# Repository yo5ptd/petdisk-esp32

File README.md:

# petdisk-esp32
CBM PETDISK based on Esp32 and MicroSD

## Introduction
My fourth PCB design, first (mostly) SMD one to test how ordering assembled PCB from JLCPCB works. Motivation for this was that it's a bit of a pain to order @bitfixer 's Petdisk Max V2 Esp32 from the US, and I've found no alternatives in the EU. 

## Hardware documentation

As per bitfixer's Petdisk V2 Max https://github.com/bitfixer/petdisk-max . Ports as per https://github.com/svenpetersen1965/PET-IEEE-488-Extension .

I've only changed the SD slot to Hanbo Electric TS-013 as this was available at JLCPCB.

### Schematic and PCB layout

[Schematic](CBM-Petdisk-Schematic.pdf)

[PCB Layout](CBM-Petdisk-Board.pdf)

[Front](petdisk%20esp32.jpg)

[Back](petdisk%20esp32-back.jpg)

## Panelization and odering from JLCPCB

Panelized with Kikit addon with hand-breakable "mousebytes", it still fits the 100x100 mm JLCPCB limit (Kikit.json settings included, details in https://github.com/yaqwsx/KiKit). 

The idea is to order the placement for the cheap SMD components, and only solder 3 electrolytic capacitors, the ESP32 module and a "805 Strip Connector 3.96mm Pitch 12 Pin" connector from Aliexpress. Cost per board from JLPCB thus is around 3.3$ when ordered in batches of 5 (10 boards in total, coupons used, shipping and taxes included) With connector, capacitors, esp32 should not get over 8.5$ per board, but probably more as I don't plan to order 10 of these.

You need the:
[Gerbers](gerbers.2xpetdisk-esp32.zip)

[BOM](BOM_JLCSMT.xlsx)

[CPL](JLCSMT_CPL.xlsx)

Disregards the duplicate message, also allow auto placement alignment.

## Programming

note that the programming port pinout is different from the original.

First board was fully assembled and tested on 29.07.2025. Note that I managed to get it working with the original Petdisk max v2.1 firmware with a 32GB card. 512mb, 1gb and 128gb cards were not recognized.

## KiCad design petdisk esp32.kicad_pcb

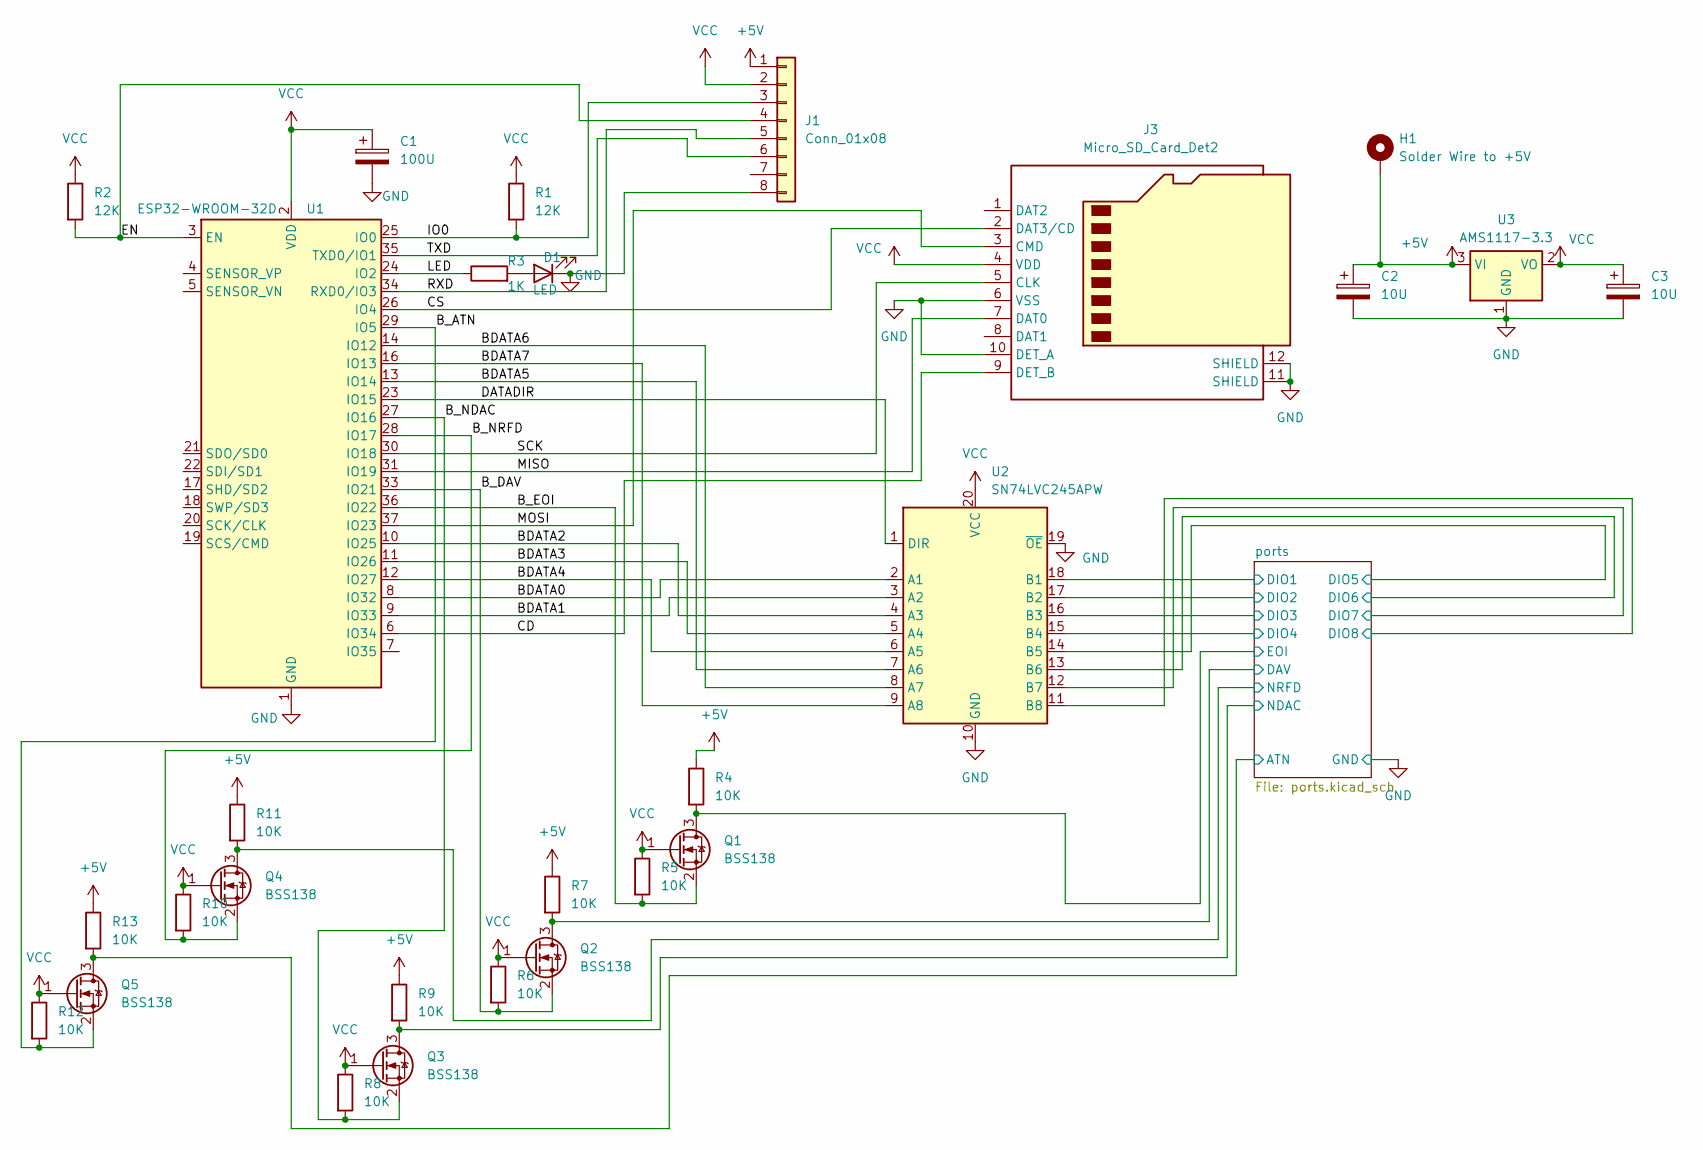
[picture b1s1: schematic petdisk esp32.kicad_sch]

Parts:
C1: 100U; CP_Radial_D5.0mm_P2.50mm
C2, C3: 10U; CP_Radial_D5.0mm_P2.50mm
D1: LED; LED_0603_1608Metric
H1: Solder Wire to +5V; SolderWire-0.1sqmm_1x01_D0.4mm_OD1mm
J1: Conn_01x08; PinHeader_1x08_P2.54mm_Vertical
J3: Micro_SD_Card_Det2; TF-SMD_TF-013
Q1, Q2, Q3, Q4, Q5: BSS138; SOT-23
R1, R2: 12K; R_0805_2012Metric
R3: 1K; R_0805_2012Metric
R4, R5, R6, R7, R8, R9, R10, R11, R12, R13: 10K; R_0805_2012Metric
U1: ESP32-WROOM-32D
U2: SN74LVC245APW; TSSOP-20_4.4x6.5mm_P0.65mm
U3: AMS1117-3.3; SOT-223-3_TabPin2

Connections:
+5V: C2.1, H1.1, J1.1, R4.1, R7.1, R9.1, R11.1, R13.1, U3.3 (VI)
/BDATA0: U1.8 (IO32), U2.2 (A1)
/BDATA1: U1.9 (IO33), U2.3 (A2)
/BDATA2: U1.10 (IO25), U2.4 (A3)
/BDATA3: U1.11 (IO26), U2.5 (A4)
/BDATA4: U1.12 (IO27), U2.6 (A5)
/BDATA5: U1.13 (IO14), U2.7 (A6)
/BDATA6: U1.14 (IO12), U2.8 (A7)
/BDATA7: U1.16 (IO13), U2.9 (A8)
/B_ATN: Q5.2 (S), R12.2, U1.29 (IO5)
/B_DAV: Q2.2 (S), R6.2, U1.33 (IO21)
/B_EOI: Q1.2 (S), R5.2, U1.36 (IO22)
/B_NDAC: Q3.2 (S), R8.2, U1.27 (IO16)
/B_NRFD: Q4.2 (S), R10.2, U1.28 (IO17)
/CD: J3.9 (DET_B), U1.6 (IO34)
/CS: J3.2 (DAT3/CD), U1.26 (IO4)
/DATADIR: U1.23 (IO15), U2.1 (DIR)
/EN: J1.4, R2.2, U1.3 (EN)
/IO0: J1.3, R1.2, U1.25 (IO0)
/LED: R3.1, U1.24 (IO2)
/MISO: J3.7 (DAT0), U1.31 (IO19)
/MOSI: J3.3 (CMD), U1.37 (IO23)
/RXD: J1.5, U1.34 (RXD0/IO3)
/SCK: J3.5 (CLK), U1.30 (IO18)
/TXD: J1.6, U1.35 (TXD0/IO1)
/ports/ATN: Q5.3 (D), R13.2; also elsewhere on the board
/ports/DAV: Q2.3 (D), R7.2; also elsewhere on the board
/ports/DIO1: U2.18 (B1); also elsewhere on the board
/ports/DIO2: U2.17 (B2); also elsewhere on the board
/ports/DIO3: U2.16 (B3); also elsewhere on the board
/ports/DIO4: U2.15 (B4); also elsewhere on the board
/ports/DIO5: U2.14 (B5); also elsewhere on the board
/ports/DIO6: U2.13 (B6); also elsewhere on the board
/ports/DIO7: U2.12 (B7); also elsewhere on the board
/ports/DIO8: U2.11 (B8); also elsewhere on the board
/ports/EOI: Q1.3 (D), R4.2; also elsewhere on the board
/ports/NDAC: Q3.3 (D), R9.2; also elsewhere on the board
/ports/NRFD: Q4.3 (D), R11.2; also elsewhere on the board
GND: C1.2, C2.2, C3.2, D1.1 (K), J1.8, J3.6 (VSS), J3.10 (DET_A), J3.11 (SHIELD), J3.12 (SHIELD), U1.1 (GND), U1.15 (GND), U1.38 (GND), U1.39 (GND), U2.10 (GND), U2.19 (~OE), U3.1 (GND); also elsewhere on the board
unnamed: D1.2 (A), R3.2
VCC: C1.1, C3.1, J1.2, J3.4 (VDD), Q1.1 (G), Q2.1 (G), Q3.1 (G), Q4.1 (G), Q5.1 (G), R1.1, R2.1, R5.1, R6.1, R8.1, R10.1, R12.1, U1.2 (VDD), U2.20 (VCC), U3.2 (VO)

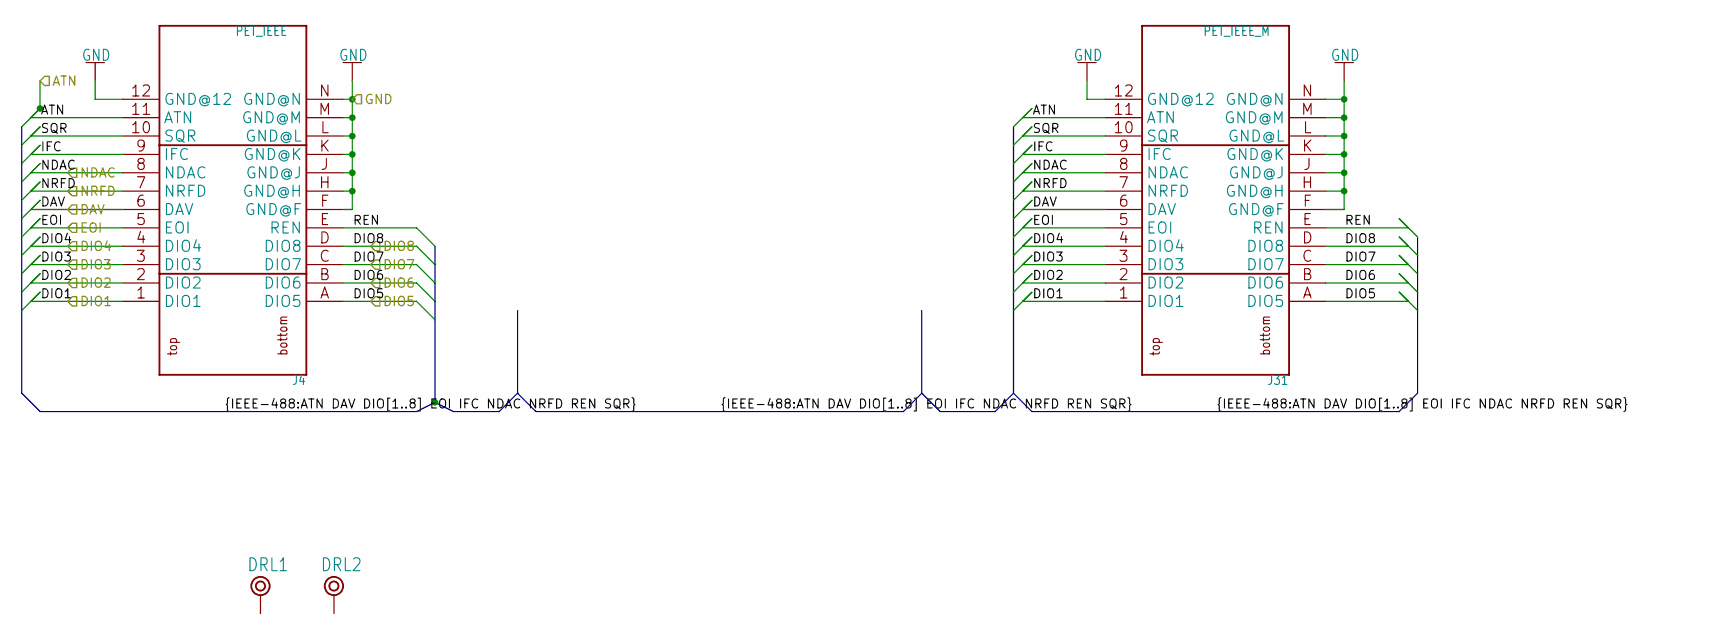
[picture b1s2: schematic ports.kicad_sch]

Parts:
DRL1, DRL2: BOHR3,5
J4: PET_IEEE; USERPORT
J31: PET_IEEE_M

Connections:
/ports/ATN: J4.11 (ATN), J31.11 (ATN); also elsewhere on the board
/ports/DAV: J4.6 (DAV), J31.6 (DAV); also elsewhere on the board
/ports/DIO1: J4.1 (DIO1), J31.1 (DIO1); also elsewhere on the board
/ports/DIO2: J4.2 (DIO2), J31.2 (DIO2); also elsewhere on the board
/ports/DIO3: J4.3 (DIO3), J31.3 (DIO3); also elsewhere on the board
/ports/DIO4: J4.4 (DIO4), J31.4 (DIO4); also elsewhere on the board
/ports/DIO5: J4.A (DIO5), J31.A (DIO5); also elsewhere on the board
/ports/DIO6: J4.B (DIO6), J31.B (DIO6); also elsewhere on the board
/ports/DIO7: J4.C (DIO7), J31.C (DIO7); also elsewhere on the board
/ports/DIO8: J4.D (DIO8), J31.D (DIO8); also elsewhere on the board
/ports/EOI: J4.5 (EOI), J31.5 (EOI); also elsewhere on the board
/ports/IFC: J4.9 (IFC), J31.9 (IFC)
/ports/NDAC: J4.8 (NDAC), J31.8 (NDAC); also elsewhere on the board
/ports/NRFD: J4.7 (NRFD), J31.7 (NRFD); also elsewhere on the board
/ports/REN: J4.E (REN), J31.E (REN)
/ports/SQR: J4.10 (SQR), J31.10 (SQR)
GND: J4.12 (GND@12), J4.F (GND@F), J4.H (GND@H), J4.J (GND@J), J4.K (GND@K), J4.L (GND@L), J4.M (GND@M), J4.N (GND@N), J31.12 (GND@12), J31.F (GND@F), J31.H (GND@H), J31.J (GND@J), J31.K (GND@K), J31.L (GND@L), J31.M (GND@M), J31.N (GND@N); also elsewhere on the board

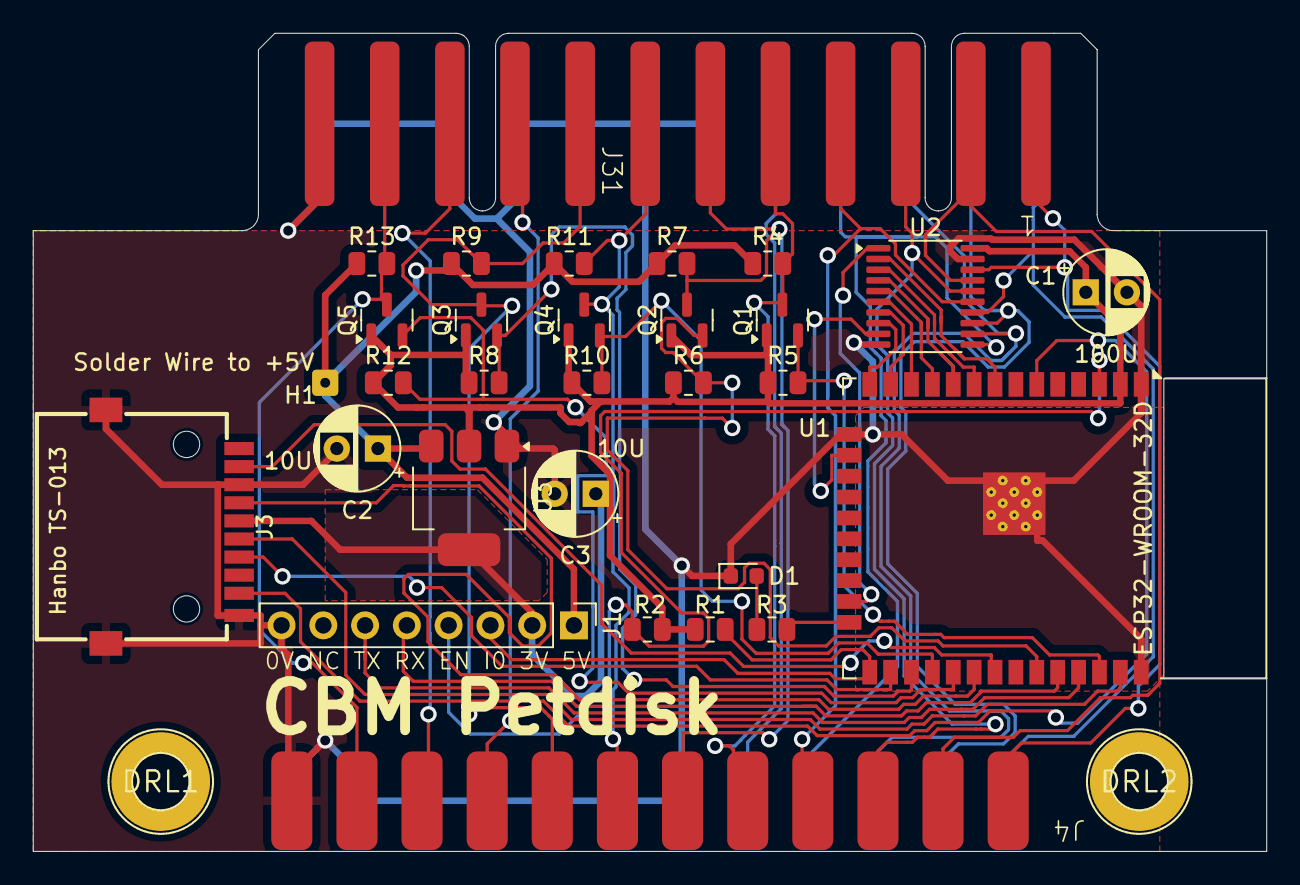
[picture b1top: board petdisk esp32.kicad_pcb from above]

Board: 2 copper layers, 75.0 x 49.8 mm, 32 parts (0 on the bottom side), 44 nets.

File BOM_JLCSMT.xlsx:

Comment | Designator | Footprint | JLCPCB Part #（optional）
10K | R7,R8,R11,R12,R4,R9,R10,R5,R6,R13 | R_0805_2012Metric | C17414
BSS138K | Q1,Q3,Q2,Q5,Q4 | SOT-23 | C8545
Micro_SD_Card_Det2 | J3 | TF-SMD_TF-013 | C961683
LED | D1 | LED_0603_1608Metric | C2286
AMS1117-3.3 | U3 | SOT-223-3_TabPin2 | C6186
12K | R1,R2 | R_0805_2012Metric | C17444
1K | R3 | R_0805_2012Metric | C17798
SN74LVC245APW | U2 | TSSOP-20_4.4x6.5mm_P0.65mm | C41361216
ESP32-WROOM-32D | U1 | ESP32-WROOM-32D | C473012

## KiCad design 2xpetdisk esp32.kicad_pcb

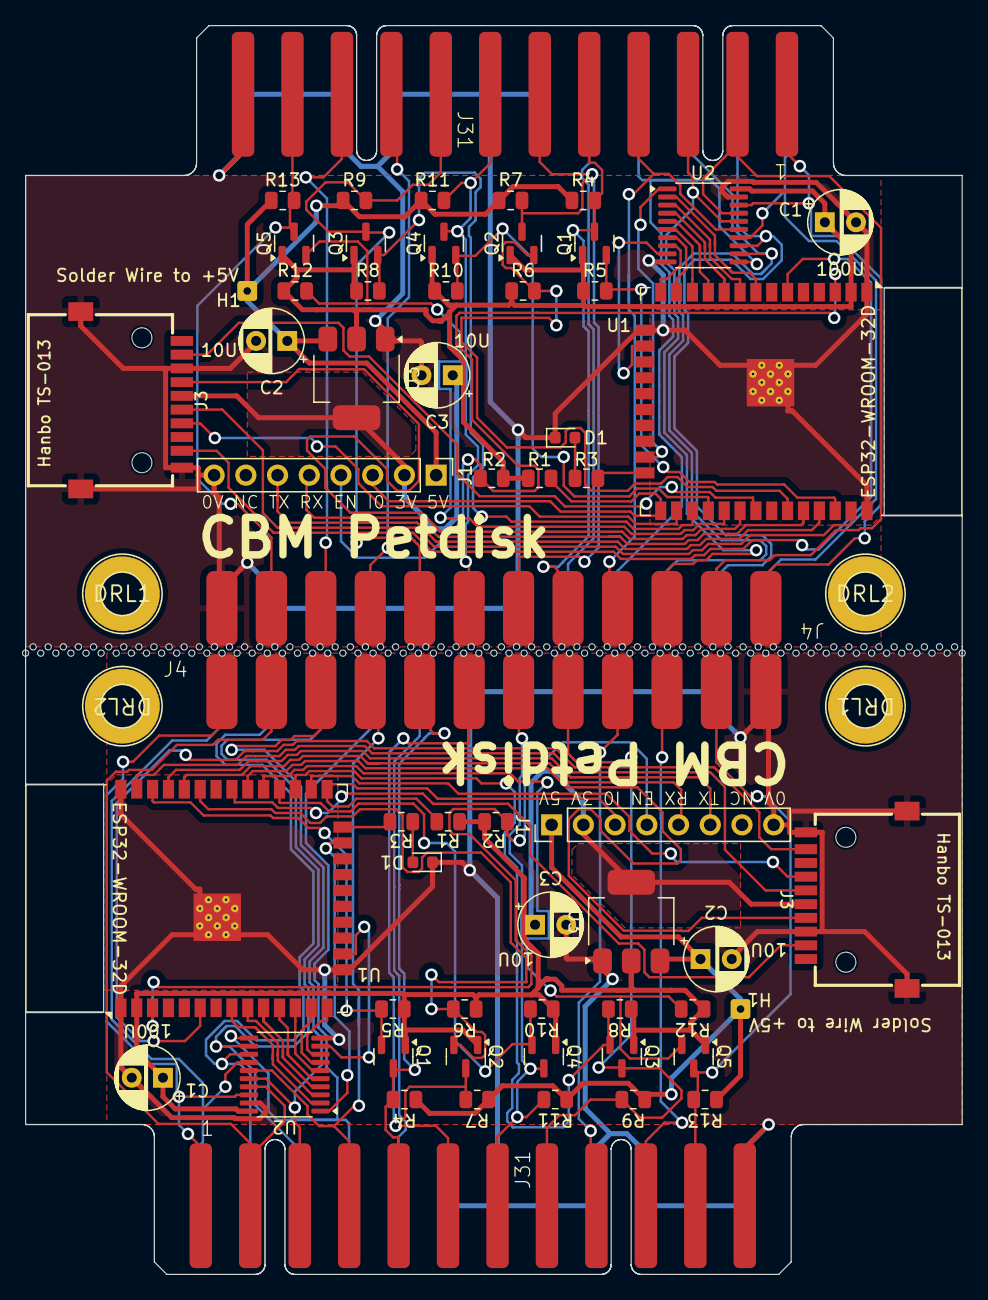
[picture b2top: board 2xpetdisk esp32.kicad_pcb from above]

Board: 2 copper layers, 75.0 x 100.0 mm, 189 parts (0 on the bottom side), 88 nets.

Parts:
C1, C1#2: 100U; CP_Radial_D5.0mm_P2.50mm
C2, C2#2, C3, C3#2: 10U; CP_Radial_D5.0mm_P2.50mm
D1, D1#2: LED; LED_0603_1608Metric
DRL1, DRL1#2, DRL2, DRL2#2: BOHR3,5
H1, H1#2: Solder Wire to +5V; SolderWire-0.1sqmm_1x01_D0.4mm_OD1mm
J1, J1#2: Conn_01x08; PinHeader_1x08_P2.54mm_Vertical
J3, J3#2: Hanbo TS-013; TF-SMD_TF-013
J4, J4#2: PET_IEEE; USERPORT
J31, J31#2: PET_IEEE_M
KiKit_MB_1_2, KiKit_MB_1_3, KiKit_MB_1_4, KiKit_MB_1_5, KiKit_MB_1_6, KiKit_MB_1_7, KiKit_MB_1_8, KiKit_MB_1_9, KiKit_MB_1_10, KiKit_MB_1_11, KiKit_MB_1_12, KiKit_MB_1_13, KiKit_MB_1_14, KiKit_MB_1_15, KiKit_MB_1_16, KiKit_MB_1_17, KiKit_MB_1_18, KiKit_MB_1_19, KiKit_MB_1_20, KiKit_MB_1_21, KiKit_MB_1_22, KiKit_MB_1_23, KiKit_MB_1_24, KiKit_MB_1_25, KiKit_MB_1_26, KiKit_MB_1_27, KiKit_MB_1_28, KiKit_MB_1_29, KiKit_MB_1_30, KiKit_MB_1_31, KiKit_MB_1_32, KiKit_MB_1_33, KiKit_MB_1_34, KiKit_MB_1_35, KiKit_MB_1_36, KiKit_MB_1_37, KiKit_MB_1_38, KiKit_MB_1_39, KiKit_MB_1_40, KiKit_MB_1_41, KiKit_MB_1_42, KiKit_MB_1_43, KiKit_MB_1_44, KiKit_MB_1_45, KiKit_MB_1_46, KiKit_MB_1_47, KiKit_MB_1_48, KiKit_MB_1_49, KiKit_MB_1_50, KiKit_MB_1_51, KiKit_MB_1_52, KiKit_MB_1_53, KiKit_MB_1_54, KiKit_MB_1_55, KiKit_MB_1_56, KiKit_MB_1_57, KiKit_MB_1_58, KiKit_MB_1_59, KiKit_MB_1_60, KiKit_MB_1_61, KiKit_MB_1_62, KiKit_MB_1_63, KiKit_MB_2_1, KiKit_MB_2_2, KiKit_MB_2_3, KiKit_MB_2_4, KiKit_MB_2_5, KiKit_MB_2_6, KiKit_MB_2_7, KiKit_MB_2_8, KiKit_MB_2_9, KiKit_MB_2_10, KiKit_MB_2_11, KiKit_MB_2_12, KiKit_MB_2_13, KiKit_MB_2_14, KiKit_MB_2_15, KiKit_MB_2_16, KiKit_MB_2_17, KiKit_MB_2_18, KiKit_MB_2_19, KiKit_MB_2_20, KiKit_MB_2_21, KiKit_MB_2_22, KiKit_MB_2_23, KiKit_MB_2_24, KiKit_MB_2_25, KiKit_MB_2_26, KiKit_MB_2_27, KiKit_MB_2_28, KiKit_MB_2_29, KiKit_MB_2_30, KiKit_MB_2_31, KiKit_MB_2_32, KiKit_MB_2_33, KiKit_MB_2_34, KiKit_MB_2_35, KiKit_MB_2_36, KiKit_MB_2_37, KiKit_MB_2_38, KiKit_MB_2_39, KiKit_MB_2_40, KiKit_MB_2_41, KiKit_MB_2_42, KiKit_MB_2_43, KiKit_MB_2_44, KiKit_MB_2_45, KiKit_MB_2_46, KiKit_MB_2_47, KiKit_MB_2_48, KiKit_MB_2_49, KiKit_MB_2_50, KiKit_MB_2_51, KiKit_MB_2_52, KiKit_MB_2_53, KiKit_MB_2_54, KiKit_MB_2_55, KiKit_MB_2_56, KiKit_MB_2_57, KiKit_MB_2_58, KiKit_MB_2_59, KiKit_MB_2_60, KiKit_MB_2_61, KiKit_MB_2_62, KiKit_MB_2_63: NPTH
Q1, Q1#2, Q2, Q2#2, Q3, Q3#2, Q4, Q4#2, Q5, Q5#2: BSS138; SOT-23
R1, R1#2, R2, R2#2: 12K; R_0805_2012Metric
R3, R3#2: 1K; R_0805_2012Metric
R4, R4#2, R5, R5#2, R6, R6#2, R7, R7#2, R8, R8#2, R9, R9#2, R10, R10#2, R11, R11#2, R12, R12#2, R13, R13#2: 10K; R_0805_2012Metric
U1, U1#2: ESP32-WROOM-32D
U2, U2#2: SN74LVC245APW; TSSOP-20_4.4x6.5mm_P0.65mm
U3, U3#2: AMS1117-3.3; SOT-223-3_TabPin2

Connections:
Board_0-+5V: C2.1, H1.1, J1.1, R4#2.1, R7.1, R9.1, R11#2.1, R13#2.1, U3#2.3 (VI)
Board_0-/BDATA0: U1#2.8 (IO32), U2#2.2 (A1)
Board_0-/BDATA1: U1#2.9 (IO33), U2#2.3 (A2)
Board_0-/BDATA2: U1#2.10 (IO25), U2#2.4 (A3)
Board_0-/BDATA3: U1#2.11 (IO26), U2#2.5 (A4)
Board_0-/BDATA4: U1#2.12 (IO27), U2#2.6 (A5)
Board_0-/BDATA5: U1#2.13 (IO14), U2#2.7 (A6)
Board_0-/BDATA6: U1#2.14 (IO12), U2#2.8 (A7)
Board_0-/BDATA7: U1#2.16 (IO13), U2#2.9 (A8)
Board_0-/B_ATN: Q5.2 (S), R12.2, U1#2.29 (IO5)
Board_0-/B_DAV: Q2.2 (S), R6#2.2, U1#2.33 (IO21)
Board_0-/B_EOI: Q1#2.2 (S), R5#2.2, U1#2.36 (IO22)
Board_0-/B_NDAC: Q3.2 (S), R8#2.2, U1#2.27 (IO16)
Board_0-/B_NRFD: Q4.2 (S), R10#2.2, U1#2.28 (IO17)
Board_0-/CD: J3.9 (DET_B), U1#2.6 (IO34)
Board_0-/CS: J3.2 (DAT3/CD), U1#2.26 (IO4)
Board_0-/DATADIR: U1#2.23 (IO15), U2#2.1 (DIR)
Board_0-/EN: J1.4, R2.2, U1#2.3 (EN)
Board_0-/IO0: J1.3, R1.2, U1#2.25 (IO0)
Board_0-/LED: R3.1, U1#2.24 (IO2)
Board_0-/MISO: J3.7 (DAT0), U1#2.31 (IO19)
Board_0-/MOSI: J3.3 (CMD), U1#2.37 (IO23)
Board_0-/RXD: J1.5, U1#2.34 (RXD0/IO3)
Board_0-/SCK: J3.5 (CLK), U1#2.30 (IO18)
Board_0-/TXD: J1.6, U1#2.35 (TXD0/IO1)
Board_0-/ports/ATN: J4#2.11 (ATN), J31#2.11 (ATN), Q5.3 (D), R13#2.2
Board_0-/ports/DAV: J4#2.6 (DAV), J31#2.6 (DAV), Q2.3 (D), R7.2
Board_0-/ports/DIO1: J4#2.1 (DIO1), J31#2.1 (DIO1), U2#2.18 (B1)
Board_0-/ports/DIO2: J4#2.2 (DIO2), J31#2.2 (DIO2), U2#2.17 (B2)
Board_0-/ports/DIO3: J4#2.3 (DIO3), J31#2.3 (DIO3), U2#2.16 (B3)
Board_0-/ports/DIO4: J4#2.4 (DIO4), J31#2.4 (DIO4), U2#2.15 (B4)
Board_0-/ports/DIO5: J4#2.A (DIO5), J31#2.A (DIO5), U2#2.14 (B5)
Board_0-/ports/DIO6: J4#2.B (DIO6), J31#2.B (DIO6), U2#2.13 (B6)
Board_0-/ports/DIO7: J4#2.C (DIO7), J31#2.C (DIO7), U2#2.12 (B7)
Board_0-/ports/DIO8: J4#2.D (DIO8), J31#2.D (DIO8), U2#2.11 (B8)
Board_0-/ports/EOI: J4#2.5 (EOI), J31#2.5 (EOI), Q1#2.3 (D), R4#2.2
Board_0-/ports/IFC: J4#2.9 (IFC), J31#2.9 (IFC)
Board_0-/ports/NDAC: J4#2.8 (NDAC), J31#2.8 (NDAC), Q3.3 (D), R9.2
Board_0-/ports/NRFD: J4#2.7 (NRFD), J31#2.7 (NRFD), Q4.3 (D), R11#2.2
Board_0-/ports/REN: J4#2.E (REN), J31#2.E (REN)
Board_0-/ports/SQR: J4#2.10 (SQR), J31#2.10 (SQR)
Board_0-GND: C1#2.2, C2.2, C3#2.2, D1.1 (K), J1.8, J3.6 (VSS), J3.10 (DET_A), J3.11 (SHIELD), J3.12 (SHIELD), J4#2.12 (GND@12), J4#2.F (GND@F), J4#2.H (GND@H), J4#2.J (GND@J), J4#2.K (GND@K), J4#2.L (GND@L), J4#2.M (GND@M), J4#2.N (GND@N), J31#2.12 (GND@12), J31#2.F (GND@F), J31#2.H (GND@H), J31#2.J (GND@J), J31#2.K (GND@K), J31#2.L (GND@L), J31#2.M (GND@M), J31#2.N (GND@N), U1#2.1 (GND), U1#2.15 (GND), U1#2.38 (GND), U1#2.39 (GND), U2#2.10 (GND), U2#2.19 (~OE), U3#2.1 (GND)
Board_0-Net-(D1-A): D1.2 (A), R3.2
Board_0-VCC: C1#2.1, C3#2.1, J1.2, J3.4 (VDD), Q1#2.1 (G), Q2.1 (G), Q3.1 (G), Q4.1 (G), Q5.1 (G), R1.1, R2.1, R5#2.1, R6#2.1, R8#2.1, R10#2.1, R12.1, U1#2.2 (VDD), U2#2.20 (VCC), U3#2.2 (VO)
Board_1-+5V: C2#2.1, H1#2.1, J1#2.1, R4.1, R7#2.1, R9#2.1, R11.1, R13.1, U3.3 (VI)
Board_1-/BDATA0: U1.8 (IO32), U2.2 (A1)
Board_1-/BDATA1: U1.9 (IO33), U2.3 (A2)
Board_1-/BDATA2: U1.10 (IO25), U2.4 (A3)
Board_1-/BDATA3: U1.11 (IO26), U2.5 (A4)
Board_1-/BDATA4: U1.12 (IO27), U2.6 (A5)
Board_1-/BDATA5: U1.13 (IO14), U2.7 (A6)
Board_1-/BDATA6: U1.14 (IO12), U2.8 (A7)
Board_1-/BDATA7: U1.16 (IO13), U2.9 (A8)
Board_1-/B_ATN: Q5#2.2 (S), R12#2.2, U1.29 (IO5)
Board_1-/B_DAV: Q2#2.2 (S), R6.2, U1.33 (IO21)
Board_1-/B_EOI: Q1.2 (S), R5.2, U1.36 (IO22)
Board_1-/B_NDAC: Q3#2.2 (S), R8.2, U1.27 (IO16)
Board_1-/B_NRFD: Q4#2.2 (S), R10.2, U1.28 (IO17)
Board_1-/CD: J3#2.9 (DET_B), U1.6 (IO34)
Board_1-/CS: J3#2.2 (DAT3/CD), U1.26 (IO4)
Board_1-/DATADIR: U1.23 (IO15), U2.1 (DIR)
Board_1-/EN: J1#2.4, R2#2.2, U1.3 (EN)
Board_1-/IO0: J1#2.3, R1#2.2, U1.25 (IO0)
Board_1-/LED: R3#2.1, U1.24 (IO2)
Board_1-/MISO: J3#2.7 (DAT0), U1.31 (IO19)
Board_1-/MOSI: J3#2.3 (CMD), U1.37 (IO23)
Board_1-/RXD: J1#2.5, U1.34 (RXD0/IO3)
Board_1-/SCK: J3#2.5 (CLK), U1.30 (IO18)
Board_1-/TXD: J1#2.6, U1.35 (TXD0/IO1)
Board_1-/ports/ATN: J4.11 (ATN), J31.11 (ATN), Q5#2.3 (D), R13.2
Board_1-/ports/DAV: J4.6 (DAV), J31.6 (DAV), Q2#2.3 (D), R7#2.2
Board_1-/ports/DIO1: J4.1 (DIO1), J31.1 (DIO1), U2.18 (B1)
Board_1-/ports/DIO2: J4.2 (DIO2), J31.2 (DIO2), U2.17 (B2)
Board_1-/ports/DIO3: J4.3 (DIO3), J31.3 (DIO3), U2.16 (B3)
Board_1-/ports/DIO4: J4.4 (DIO4), J31.4 (DIO4), U2.15 (B4)
Board_1-/ports/DIO5: J4.A (DIO5), J31.A (DIO5), U2.14 (B5)
Board_1-/ports/DIO6: J4.B (DIO6), J31.B (DIO6), U2.13 (B6)
Board_1-/ports/DIO7: J4.C (DIO7), J31.C (DIO7), U2.12 (B7)
Board_1-/ports/DIO8: J4.D (DIO8), J31.D (DIO8), U2.11 (B8)
Board_1-/ports/EOI: J4.5 (EOI), J31.5 (EOI), Q1.3 (D), R4.2
Board_1-/ports/IFC: J4.9 (IFC), J31.9 (IFC)
Board_1-/ports/NDAC: J4.8 (NDAC), J31.8 (NDAC), Q3#2.3 (D), R9#2.2
Board_1-/ports/NRFD: J4.7 (NRFD), J31.7 (NRFD), Q4#2.3 (D), R11.2
Board_1-/ports/REN: J4.E (REN), J31.E (REN)
Board_1-/ports/SQR: J4.10 (SQR), J31.10 (SQR)
Board_1-GND: C1.2, C2#2.2, C3.2, D1#2.1 (K), J1#2.8, J3#2.6 (VSS), J3#2.10 (DET_A), J3#2.11 (SHIELD), J3#2.12 (SHIELD), J4.12 (GND@12), J4.F (GND@F), J4.H (GND@H), J4.J (GND@J), J4.K (GND@K), J4.L (GND@L), J4.M (GND@M), J4.N (GND@N), J31.12 (GND@12), J31.F (GND@F), J31.H (GND@H), J31.J (GND@J), J31.K (GND@K), J31.L (GND@L), J31.M (GND@M), J31.N (GND@N), U1.1 (GND), U1.15 (GND), U1.38 (GND), U1.39 (GND), U2.10 (GND), U2.19 (~OE), U3.1 (GND)
Board_1-Net-(D1-A): D1#2.2 (A), R3#2.2
Board_1-VCC: C1.1, C3.1, J1#2.2, J3#2.4 (VDD), Q1.1 (G), Q2#2.1 (G), Q3#2.1 (G), Q4#2.1 (G), Q5#2.1 (G), R1#2.1, R2#2.1, R5.1, R6.1, R8.1, R10.1, R12#2.1, U1.2 (VDD), U2.20 (VCC), U3.2 (VO)

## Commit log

2025-06-27 Initial
2025-06-27 JLCPCD order
2025-06-27 Added readme, images, pdf, gerber (zip).
2025-06-28 Files ordered from JLCPCB.
    connector silkscreen fix
2025-06-28 Update README with warning that board is still untested
2025-07-16 Small touchup
2025-07-29 Removed untested message.
2025-08-13 3D printed case based on YAPP
    openscad
